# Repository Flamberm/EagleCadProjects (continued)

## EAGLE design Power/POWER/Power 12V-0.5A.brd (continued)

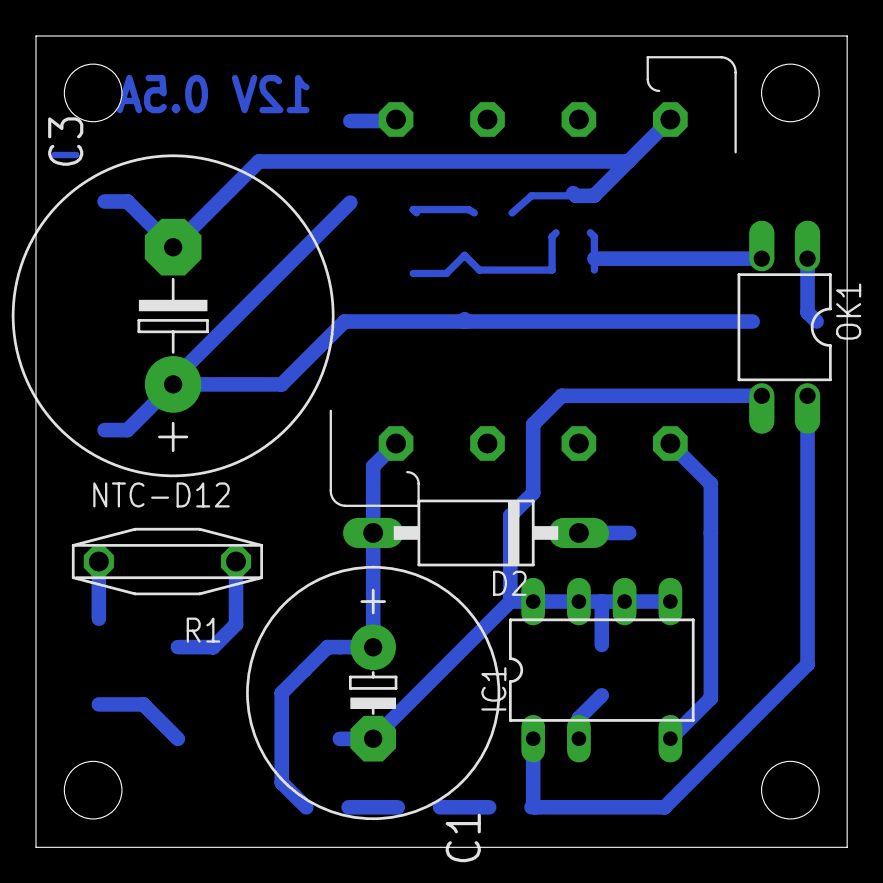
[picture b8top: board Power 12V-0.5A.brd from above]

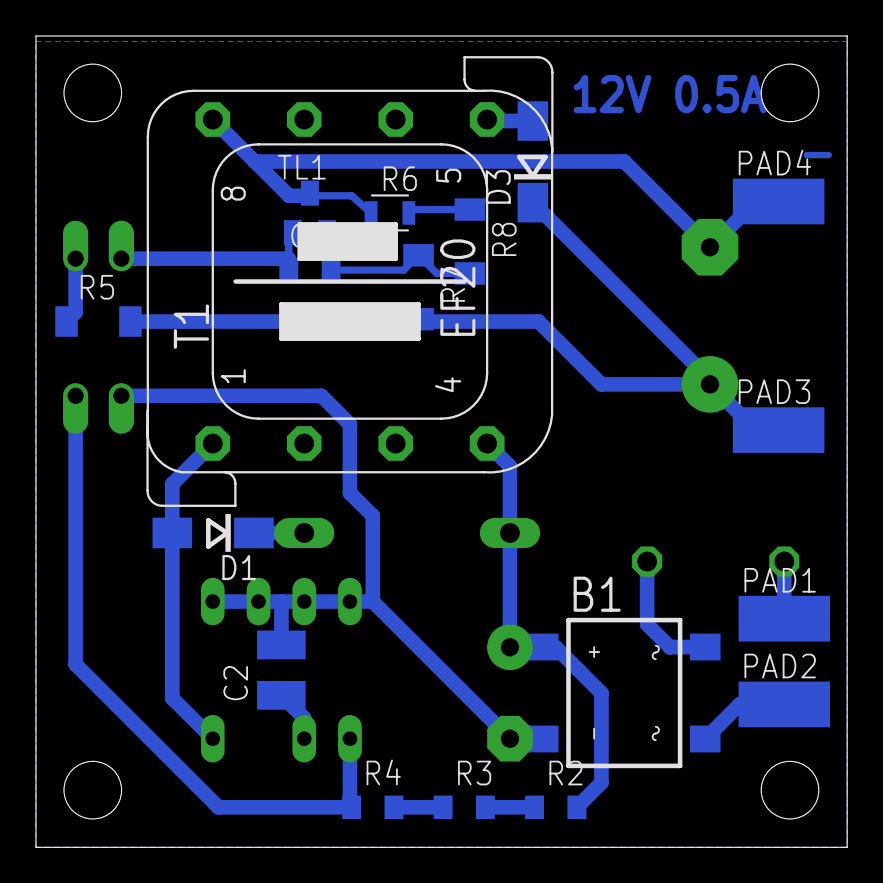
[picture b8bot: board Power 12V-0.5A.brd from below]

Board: 2 copper layers, 45.1 x 45.1 mm, 24 parts (18 on the bottom side), 18 nets.

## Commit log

2016-07-18 :space_invader: Added .gitattributes & .gitignore files
2016-07-18 Initial Create Repo
2016-07-18 Изменения в обратной связи схеме драйвера
    Резисторы в базах мосфетов заменены на выводные, изменена разводка
    обратной связи в районе TL431
2016-07-19 Добавил диод параллельно двигателю
2016-07-21 перераспределение
2016-07-25 Исправил ошибки
    Всё равно что-то не работет
2016-07-27 TNY Flyback
2016-07-27 Регулятор
2016-08-01 Опять переделка
2016-08-02 Добавил нагрузочный резистор оп 24В линии
2016-08-09 предельное упрощение платы
2016-08-09 Printer power
    Initial
2016-08-10 Правки платы и обозначений
2016-08-14 Начало перестройки
2016-08-18 ПерваЯ попытка развода
2016-08-19 Продолжение
    Развёл дежурку, немного упростил плату TL494
2016-08-28 Noise
2016-09-02 _ненужное
2016-09-09 Lab Power
2016-09-12 Noise Maker
2016-09-16 Блок для нихрома
2016-09-21 Ignore Eagle Backups
2016-10-01 Some Changes
2016-10-20 Final design
    I hope...
2016-10-21 PS for Solder
2016-10-21 Some laser refactor
2016-11-01 Some CO2 reverse
2016-11-07 Feedback Amp with INA168
    Testing test
2016-11-14 Опять всё неправильно сделал
2016-11-19 Printer Power
2016-11-28 DeskLamp
2016-11-28 Люстры
2016-11-30 Lustre
2016-11-30 Ready
2016-12-05 Люстра-Ламп
2016-12-05 Люстр-дров
2016-12-05 Not ignore
2016-12-06 Projects
2016-12-07 Не уверен
2016-12-09 Flash
2016-12-10 More Flash
2016-12-14 Large Flash
2016-12-19 Step-Down test
2016-12-19 Some minor changes
2016-12-25 Новая выжигалка
2016-12-26 Аккуратность
2016-12-31 Перделка
    Надо всё переделать
2017-01-16 Power
2017-01-18 "Лазер"
2017-01-21 Monitor23
2017-01-21 Static
2017-01-22 Термореле
2017-01-22 Тщшыу
2017-01-30 AAAaaaa!
2017-01-31 мост на N-мосфетах, Logic Level
2017-01-31 Noise... Again...
2017-01-31 and again...
2017-01-31 Simple STLink
2017-02-01 Ещё немного
2017-02-03 Хорошо
2017-02-04 Bridge
2017-02-05 Термометр
2017-02-16 STM32F030
2017-02-16 V-REC
2017-02-17 HOLES! Bow-chica-bow-wow
2017-02-19 The LAMP
2017-02-19 More Bread
2017-03-07 Mmmm...Bread...
2017-03-15 _Something
2017-03-20 PrusaHeatbed
2017-03-21 Some 1280
2017-03-27 полная ардуйня
2017-04-05 Done
2017-04-07 Some Tweaks
2017-04-11 Всё перделать
2017-04-13 Motor
2017-04-16 Cleaning
2017-04-17 Лампочка
2017-04-23 Some lamps
2017-04-23 3Dprint
2017-05-01 Some printer adapter
2017-05-02 Adapter for custom
2017-05-02 SD-Card
2017-05-02 All burned
2017-05-03 Принтер реворк
2017-05-04 Надеюсь последние
2017-05-04 Noooooizzee
2017-05-05 Stupid mistake
2017-05-05 Быстро сделал хрень
2017-05-11 Modular Lamb
2017-05-11 Туалетный драйвер
2017-05-17 Перделка перделки
2017-05-17 Что-то изменилось
2017-06-18 SMPS
2017-06-21 CapPol
2017-06-23 some
2017-06-27 HV LED Driver
2017-06-30 POE Injector
2017-07-06 TF-CARD
2017-07-19 Smoother
2017-07-29 New LED CCS
2017-07-31 Оптостоп
2017-07-31 Лампа Паука
2017-08-02 Драйвер паучей люстры
2017-08-08 Torch
2017-08-09 Some Minor Changes
    В связи с возможностью синхронизации с Фуженом
2017-08-14 Motor Measures
2017-08-14 Motor Fine Touches (Still messy)
2017-08-28 New PSU
2017-08-28 StandBy Supply
2017-08-28 Something
2017-09-06 Горячая сторона
2017-09-14 Всё неправильно
2017-09-15 Вроде готово
2017-09-15 как всегда
2017-09-23 OptoBed
2017-09-23 Небольшие правки
2017-09-24 Правки
2017-09-24 исправил существенные косяки
2017-09-24 Зенер был бредом
2017-10-19 True Optostop
2017-10-20 OctoPower
2017-11-12 Внешние драйвера для MKS SBASE
2017-11-12 Доработки к внешним драйверам
2017-11-12 Так всем будет лучше
2017-11-23 Тёщина люстра-перделка
2017-12-14 Ethernet
2017-12-17 Гирлянда
2017-12-18 мелкие правки
2017-12-22 !не вывел пины питания!
2018-01-23 PSU for single cooler
2018-01-28 Всякое
2018-01-30 Thermo
2018-02-13 TMC OTP
2018-02-13 LEDline
2018-03-22 Some Charger
    Missing low voltage OP-AMP
2018-03-22 Added some info
2018-03-22 DO NOT
2018-04-10 более универсально
2018-04-11 Some Power
2018-04-13 Optorelay
2018-04-20 new version
2018-05-18 KeyPad
2018-05-19 Хруень
2018-05-21 more accurate
2018-06-07 For Welder
2018-06-09 Теперь работает
2018-07-07 Eagle 9.1
2018-07-08 NEW KEY
2018-07-08 что-то ошло не так
2018-07-08 Выносной USB
2018-07-12 TurboTest
2018-07-12 TurboTestTrue
2018-07-13 Eagle Version
2018-07-19 Pogopins
2018-07-31 Gateron
2018-08-09 Keyboard
2018-08-17 New UV
2018-09-20 PocketLamp
2018-09-28 KitchenTimer
2018-10-13 Термопара+Реле
2018-10-17 some minpr changes
2018-10-17 Library Changes
2018-10-17 Some Library Changes
2018-11-02 Another Driver Board
2018-11-02 Driver Board
2018-11-02 Multiply
2018-11-03 Some Compacting
2018-11-11 Хрень
2018-11-12 Исправил микросхему
2018-11-18 Монитор
2018-11-21 Inverted Driver Board
2018-11-23 The Begining
2018-11-26 Почти
2018-11-26 Наконец
2018-12-03 Очередной монитор
2018-12-04 Понемногу
2018-12-07 Релиз
2019-07-01 Преобразователь уровней
2019-07-02 Блок питания 5В 12В
2019-07-14 Зачаток прокладки
2019-07-15 Готово?
2019-07-24 100mA 210V
2019-07-25 Программатор?
2019-07-26 Панелька
2019-10-03 03,10
2021-04-01 MKS PWC
2021-04-04 HallStop
